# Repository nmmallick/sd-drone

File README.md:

# sd-drone
Team 4 senior design project - Intuitive Drone Controls
Intuitive Drone Controls
Project Description:
An FPV drone that takes in user commands via a wearable mask.
Project Specifications
• The FPV drone should take in user input via a(n) gyroscope/accelerometer attached
to a wearable mask.
• The user commands the drone movement by head tilts: fore and aft, side to side, and
up and down.
• The drone must be in stable flight.
• Any other "normal" drone features are to be retained and handless.

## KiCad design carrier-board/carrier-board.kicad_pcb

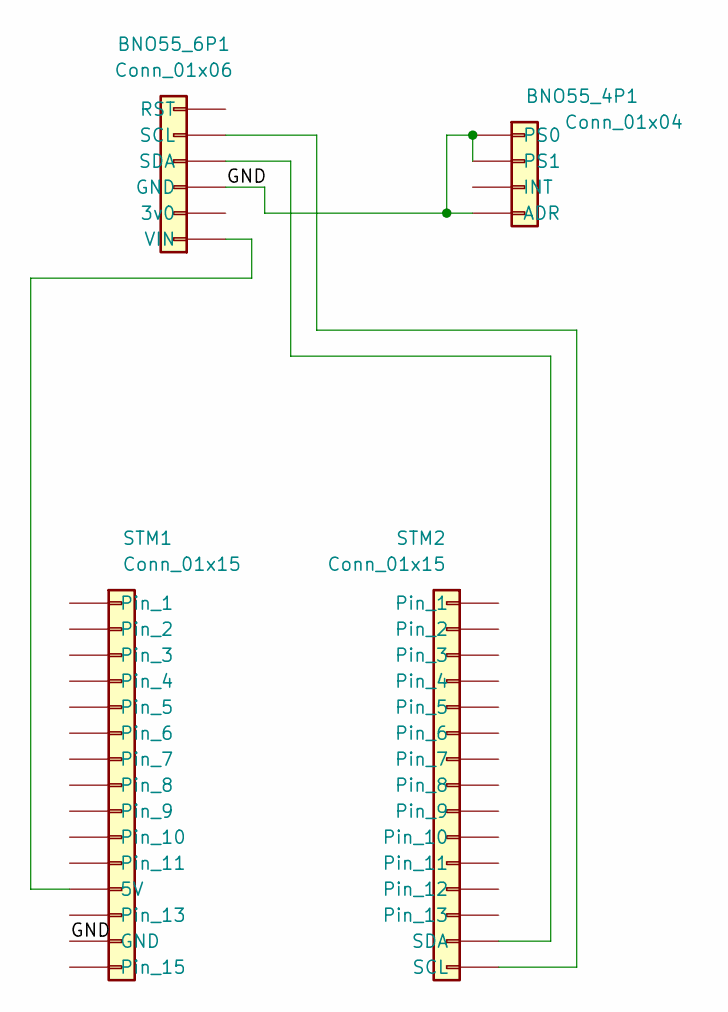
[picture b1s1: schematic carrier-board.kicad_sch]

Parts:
BNO55_4P1: Conn_01x04; PinSocket_1x04_P2.54mm_Vertical
BNO55_6P1: Conn_01x06; PinSocket_1x06_P2.54mm_Vertical
STM1, STM2: Conn_01x15; PinSocket_1x15_P2.54mm_Vertical

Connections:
/GND: BNO55_4P1.1 (PS0), BNO55_4P1.2 (PS1), BNO55_4P1.4 (ADR), BNO55_6P1.3 (GND), STM1.14 (GND)
unnamed: BNO55_6P1.1 (VIN), STM1.12 (5V)
unnamed: BNO55_6P1.4 (SDA), STM2.14 (SDA)
unnamed: BNO55_6P1.5 (SCL), STM2.15 (SCL)

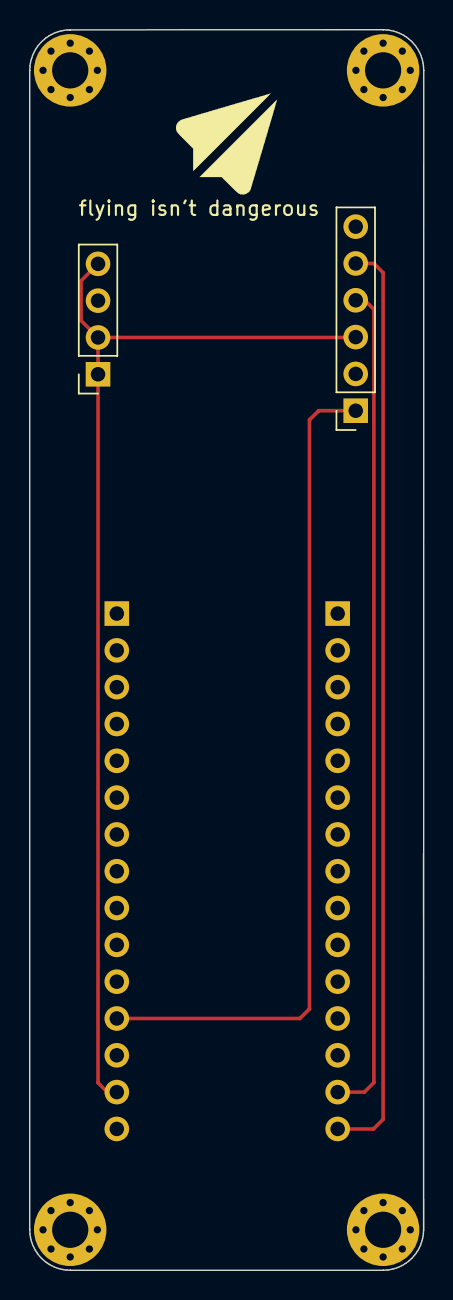
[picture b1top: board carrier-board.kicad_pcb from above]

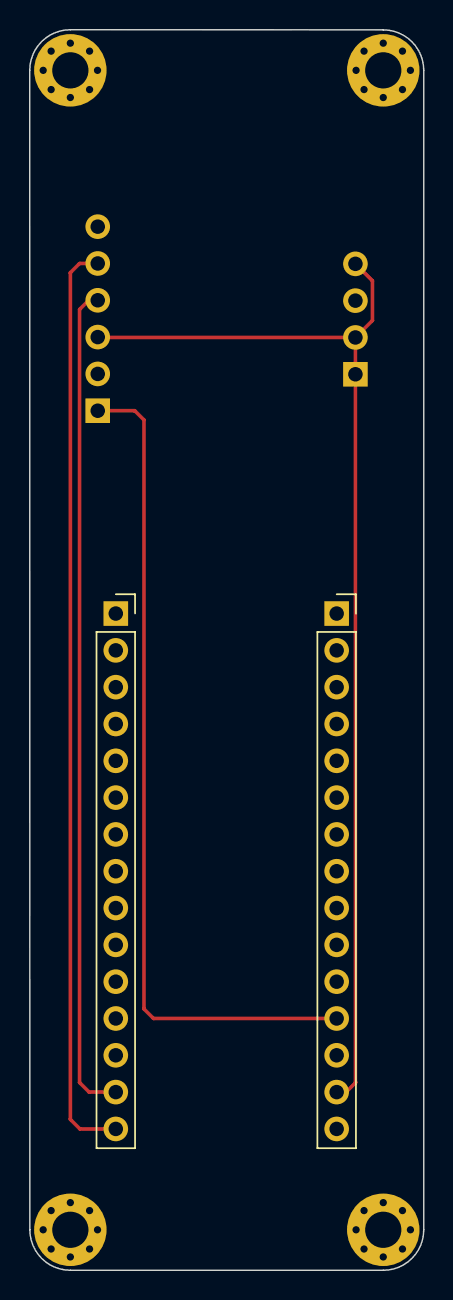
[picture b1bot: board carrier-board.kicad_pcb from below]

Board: 2 copper layers, 27.2 x 85.6 mm, 9 parts (2 on the bottom side), 4 nets.

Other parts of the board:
G**: LOGO
REF1, REF2, REF3, REF4: MountingHole_2.5mm_Pad_Via

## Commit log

2023-09-19 init stm-imu module
2023-09-20 excluding emacs backup files in gitignore
2023-09-20 adding imu drivers for bno055
2023-09-21 added i2c gyroscope interface
2023-09-21 added build dir to .gitignore
2023-09-21 another emacs backup file for gitignore
2023-09-21 impl for imu reads and init
2023-10-01 added base defconfig for rpi buildroot recipe
2023-10-02 reconfigured stm project for blue pill processor
2023-10-03 fixing imu serial interface
2023-10-04 cubeMX config change
2023-10-04 added printf float support for debugging
2023-10-04 first iter of imu interface + imu debugging
2023-10-05 adding more emacs ignores
2023-10-05 added cmatrix repo submodule
2023-10-05 added quaternion and euler angle types, added conversions for both
2023-10-08 added CMSIS library for mat functions
2023-10-08 see prev commit
2023-10-08 build impl of kalman filter for attitude estimation
2023-10-08 added more BNO055 register mappings
2023-10-08 adding source and header locations for CMSIS
2023-10-08 remove cmatrix
2023-10-08 set uart to send quaternion buffer
2023-10-08 ignore python caching
2023-10-08 added visualization implementation
2023-10-08 Update README.md for visualization module
2023-10-09 fixing submodule remote
2023-10-09 fixing submodules url
2023-10-09 fixing path for submodule
2023-10-09 re-initializing submodule
2023-10-09 printing our euler angles in attitude visualization
2023-10-12 added support for stm32l432
2023-10-13 Basic TCP server
    get saved data
    echo message
    toggle_led r,g,b - updates 3 values at once
    exit - disconnect client
    kill - off
2023-10-13 rpi-client
    connects to BT connection (slave)
    sends TCP updates - manually or when receiving data
2023-10-13 arduino_input_sim
    sends BT serial message out anytime a variable is changed
2023-10-14 added main function to sread.py
2023-10-14 ported the attitude estimation to stm32l4 chip
2023-10-17 fixed attitude estimator firmware
2023-10-17 added signaling sync for serial rad
2023-10-19 init commit for offboard branch
2023-10-19 made interface for udp socket and extracting data
2023-10-25 init offboard impl with a few utillity functions
2023-10-30 set the conncection url to be the actual fc
2023-10-31 initializing buildroot stuff
2023-11-10 removed buildroot things and impl of system
2023-11-13 working implementation of the drone control system
2023-11-13 added basic python scripts for communicating controls via socket
2023-11-15 checked in kicad project for carrier board
2023-11-17 added gpio for leds
2023-11-17 print debug statement for led loop
2023-11-17 setup for led pins
2023-11-17 removed pot pin
2023-11-17 modified gpio pins to bcm convention
2023-11-17 fixed led toggling and changed print statements to reflet button purpose
2023-11-17 added arm switch
2023-11-17 added pin
2023-11-20 added test dir
2023-11-20 build setup and compile error fixes for arm_drone test
2023-11-21 removed commented code and refactored arming tests
2023-11-21 seperated files for interfaces
2023-11-21 build offboard target as library
2023-11-21 added takeoff and land test
2023-11-22 added require rc toggling and build changes
2023-12-01 refactoring bno driver
2023-12-01 correct configuration for r/p/y
2023-12-01 added offset computation on startup, configured correct gpio
2023-12-01 forgot to uncomment rpi specific modules
2023-12-01 emacs messed up some syntax, not me
2023-12-01 removed unwanted stdlib header
2023-12-01 added configurations for stable control tuning
2023-12-07 override rc check
